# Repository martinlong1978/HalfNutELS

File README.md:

# HalfNutELS — Electronic Leadscrew

An open-source **Electronic Leadscrew (ELS)** controller for a metalworking lathe, running on an
**ESP32-WROOM-32E**, with a 320×240 LVGL TFT interface, a 3×3 keypad and a rotary encoder.

An electronic leadscrew replaces a lathe's mechanical change gears / gearbox. Instead of a train of
gears mechanically coupling the spindle to the leadscrew, an **encoder** on the spindle is read by
the microcontroller, which drives a **stepper motor** on the leadscrew in software-defined ratio to
the spindle. This lets you select any thread pitch or feed rate electronically — for single-point
threading and powered feeding — without swapping gears.

> **Note on the name:** *half-nuts* are the split nut a lathe operator clamps onto the leadscrew to
> engage a threading pass — and the part an electronic leadscrew makes redundant, since the pitch is
> now held in software rather than caught on a thread-dial line. The project was called *TeensyELS*
> until August 2026, after the Teensy it began on; Teensy support was removed well before the rename,
> and naming firmware after its microcontroller was a poor idea in the first place. The upstream
> project it derives from is still called TeensyELS — see [Attribution](#attribution). The KiCad
> projects and the board silkscreen also still carry the old name.

> **Note on the hardware:** the current design is the **LVGL board** in
> [`kicad/LVGL/`](kicad/LVGL/) (silkscreened `TeensyELS v0.6`, pre-rename) — an ESP32-WROOM-32E
> soldered directly to the board, driving a 320×240 SPI TFT through LVGL. It is the only board design
> in the repository — the earlier revisions have been removed.

---

## Contents
- [Features](#features)
- [Hardware / Components](#hardware--components)
- [Enclosure & keycaps](#enclosure--keycaps)
- [Getting boards made (PCB)](#getting-boards-made-pcb)
- [Building & flashing the firmware](#building--flashing-the-firmware)
- [Connecting & configuring](#connecting--configuring)
- [Operating the ELS — controls & display](#operating-the-els--controls--display)
- [Cutting a thread](#cutting-a-thread)
- [Firmware updates](#firmware-updates)
- [Settings reference](#settings-reference)
- [Diagnostics](#diagnostics)
- [Testing / development](#testing--development)
- [License](#license)
- [Attribution](#attribution)
- [Safety disclaimer](#safety-disclaimer)

---

## Features

- **Threading** — synchronise the leadscrew to the spindle at a selectable thread pitch for
  single-point threading. Metric (mm/rev) and imperial (TPI) thread pitch tables are built in.
- **Reverse threading** — a thread mode that runs the carriage in the opposite direction (from the
  left stop toward the right) for left-hand threads or threading away from a shoulder.
- **Feeding** — powered feed at a selectable feed rate (mm/rev metric, or thou/rev imperial).
- **Feed / thread mode switching** from the panel; **metric / imperial** from the menu.
- **Jog** — move the carriage left/right under power. Supports both an interactive "hold to jog"
  mode and a "jog to stop" mode.
- **End stops / stop positions** — set left and right stop positions so the carriage automatically
  decelerates and stops at a repeatable point (useful for threading up to a shoulder).
- **Thread sync** — the leadscrew tracks the spindle's angular position so a partially cut thread can
  be picked up again on the next pass.
- **Motion lockout** — while the carriage is under power the panel answers only **HALT** and
  **ENABLE**. There is no lock key to remember: the machine locks itself exactly when it matters.
  (This replaced an explicit button lock, which had to be unlocked at every power-on.)
- **DRO** — carriage position referenced to an endstop, with a travel bar that doubles as a readout.
- **Dark and light themes**, selectable on the device.
- **Web-based configuration** — all lathe parameters (encoder PPR, stepper PPR, gearbox ratio,
  leadscrew pitch, speeds, acceleration) plus WiFi credentials are configured over a built-in web
  page; settings are stored in the ESP32's non-volatile flash.
- **Over-the-air (OTA) firmware update** — pulls the latest [GitHub release](https://github.com/martinlong1978/HalfNutELS/releases)
  from a stable permalink and skips the download if the device is already on that version.
- **Motion-trace capture** — records ~25 s of following error, loop timing and spindle deltas and
  uploads it as CSV for offline analysis. Built to diagnose a threading glitch; kept because it is
  the fastest way to answer "is the fault in the maths or in the timing?".
- **On-device display** — a 240×320 ST7789 SPI TFT, driven in landscape (**320×240**) via **LVGL**,
  shows current mode, pitch, spindle RPM and status.
- **Rotary encoder** — turns to adjust whatever the panel currently has focused; its
  built-in LED shows the run state at a glance (the firmware drives the red and green channels,
  alternating them to flash a two-colour status).

---

## Hardware / Components

The controller is built around a custom PCB. KiCad design files, gerbers and fabrication outputs are
in the [`kicad/`](kicad/) directory.

**The current design is [`kicad/LVGL/`](kicad/LVGL/)** — silkscreened *TeensyELS v0.6*, a **4-layer**
board of roughly **113 × 109 mm**. It does not socket a dev-board module: the **ESP32-WROOM-32E is
soldered directly to the PCB**, the display is a separate SPI TFT module on a 14-pin socket, and the
board is designed to be **SMT-assembled** (JLCPCB) with only the connectors and the rotary encoder
hand-soldered.

### Bill of materials

**SMT parts** — taken from the JLCPCB production BOM
([`kicad/LVGL/jlcpcb/production_files/BOM-TeensyELS.csv`](kicad/LVGL/jlcpcb/production_files/BOM-TeensyELS.csv)),
cross-checked against the schematic:

| Designator(s) | Qty | Part / Value | Footprint | LCSC |
|---|---|---|---|---|
| U2 | 1 | **ESP32-WROOM-32E** — main controller (Wi-Fi module, 4 MB flash) | ESP32-WROOM-32D | C701342 |
| U1 | 1 | AMS1117-3.3 — 5 V → 3.3 V regulator | SOT-223-3 | C6186 |
| Q2–Q7, Q9 | 7 | BSS138 N-channel MOSFET (3.3 V ↔ 5 V level shifting, LED drive) | SOT-23 | C7420339 |
| C1 | 1 | 10 µF capacitor | 0805 | C15850 |
| C2 | 1 | 22 µF capacitor | 0805 | C45783 |
| C3, C4 | 2 | 0.1 µF capacitor | 0805 | C49678 |
| R1–R8, R11, R12, R17, R18, R20, R21 | 14 | 10 kΩ resistor (pull-ups) | 0805 | C17414 |
| R9, R10, R19 | 3 | 330 Ω resistor (encoder LED series) | 0805 | C17630 |
| R13, R14 | 2 | 0 Ω link (encoder direct-connect option) | 0805 | C17477 |
| SW1–SW10 | 10 | Omron B3FS-101xP **SMD** tactile switch (SW2–SW10 = the 3×3 keypad; SW1 = stepper-enable override) | SW_SPST_Omron_B3FS-101xP | C231324 |
| J5 | 1 | 2×3 1.27 mm header — UART programming header | PinHeader 2x03 1.27 mm SMD | C42372553 |

**Not fitted (DNP)** — an alternative encoder input path, see the note below:

| Designator(s) | Qty | Part / Value |
|---|---|---|
| Q1, Q8 | 2 | BSS138 (encoder level-shift MOSFETs) |
| R15, R16 | 2 | 1 kΩ (gate resistors for Q1/Q8) |

**Through-hole / hand-soldered parts** — these are *not* in the assembly BOM and must be fitted
yourself:

| Designator | Qty | Part | Purpose |
|---|---|---|---|
| J1 | 1 | Shielded RJ45 jack (RCH RC01937) | **Stepper driver** — step / dir / enable / alarm, at 5 V |
| J2 | 1 | JST-XH 4-pin vertical header (B4B-XH-A) | **Spindle encoder** — 5 V, GND, A, B |
| J3 | 1 | 1×14 2.54 mm socket | **Display module** (see below) |
| J4 | 1 | 2-pin 5.08 mm screw terminal (CUI TB007-508-02) | **5 V power input** |
| E1 | 1 | Illuminated (RGB) rotary encoder, SparkFun footprint | Pitch / jog-rate selection + status LED |

Not on the board at all, but **required to build a working ELS**:

- A **240×320 SPI TFT module** with the common **14-pin 2.54 mm header** (9 display pins + 5 touch
  pins). The firmware drives it as an **ST7789** and uses it in landscape, 320×240. Only the display
  pins are wired — the 5 touch pins are unconnected, and the backlight pin is tied to +3.3 V, so the
  backlight is permanently on and is *not* under software control.
- A **spindle encoder** — a quadrature encoder on the lathe spindle, wired to **J2** (not J1). The
  default configuration assumes **1200 PPR** (see [Settings reference](#settings-reference)).
- A **stepper motor + driver** for the leadscrew, wired to the RJ45 jack **J1**. The board provides
  step, dir and enable as 5 V open-drain outputs (10 kΩ pull-ups to +5 V) and accepts the driver's
  alarm output. The default configuration assumes a **400 step/rev** stepper.
- A **5 V supply** into J4 (which also feeds the encoder and the 3.3 V regulator), plus a suitable
  **power supply for the stepper driver** itself.
- A **USB-to-serial adapter** for flashing — the board has no USB connector, see
  [Building & flashing](#building--flashing-the-firmware).

> **Encoder input — 3.3 V vs 5 V.** J2's A/B pins can reach the ESP32 two ways: directly through the
> 0 Ω links **R13/R14**, or level-shifted through **Q1/Q8 + R15/R16**. The assembly BOM fits the 0 Ω
> links and leaves the MOSFET path off, i.e. it expects an encoder whose outputs are safe to feed
> straight into a 3.3 V GPIO. If your encoder swings to 5 V, fit Q1/Q8 and R15/R16 and leave R13/R14
> off. **Please verify against the schematic** ([`kicad/LVGL/TeensyELS.kicad_sch`](kicad/LVGL/TeensyELS.kicad_sch))
> before ordering.

### Connectors

| Ref | Type | Pinout |
|---|---|---|
| **J4** | 2-pin screw terminal | 1 = GND, 2 = **+5 V in** |
| **J2** | JST-XH 4-pin | 1 = +5 V, 2 = GND, 3 = encoder B, 4 = encoder A |
| **J1** | RJ45 (shielded) | 1 = ALARM (in), 3 = ENABLE, 5 = DIR, 7 = STEP; 2/4/6/8 = GND; shield = GND. All 5 V. |
| **J3** | 1×14 socket (display) | 14 = VCC, 13 = GND, 12 = CS, 11 = RESET, 10 = DC, 9 = MOSI, 8 = SCK, 7 = LED (tied to +3.3 V), 6 = MISO (not connected to the ESP32); 5–1 = touch pins, unconnected |
| **J5** | 2×3 1.27 mm | 1 = EN, 2 = +3.3 V, 3 = TXD, 4 = GND, 5 = RXD, 6 = BOOT (GPIO0) |
| **SW1** | on-board push button | Pulls the stepper **ENABLE** line to +5 V — a manual override, independent of the firmware |

### Pin assignments (ESP32)

Defined in [`lib/config/board.h`](lib/config/board.h) and matching the LVGL schematic:

| Function | GPIO |
|---|---|
| Spindle encoder A / B (J2) | 35 / 34 |
| UI rotary encoder A / B (E1) | 39 / 36 |
| Encoder status LED — red / green / blue (E1) | 22 / 21 / 12 |
| Leadscrew step | 25 |
| Leadscrew direction | 26 |
| Stepper enable | 17 |
| Stepper driver alarm input | 27 *(wired on the board; not read by the current firmware)* |
| Keypad matrix rows (H1/H2/H3) | 32 / 33 / 2 |
| Keypad matrix columns (V1/V2/V3) | 13 / 14 / 15 |
| TFT display (MOSI/SCLK/CS/DC/RST) | 19 / 18 / 5 / 16 / 23 |
| TFT backlight (`TFT_BL`) | 4 *(defined in the build flags but **not connected** on this board)* |
| Programming UART TXD / RXD (J5) | 1 / 3 |

> The A/B pins of both encoders are swapped in `board.h` relative to the schematic net names — that
> only sets which way round the counting goes, and is deliberate.

> **The keypad matrix is polled, not interrupt-driven.** A 2 ms task scans it and a host-tested
> debounce ([`lib/keyscan/`](lib/keyscan/)) turns the readings into press / click / hold / release
> events. Edge interrupts were tried and removed — see [`docs/keypad-audit.md`](docs/keypad-audit.md)
> for why they cannot be made reliable here.

---

## Enclosure & keycaps

Two 3D models are provided in [`cad/`](cad/), both as **STEP** files:

| File | What it is |
|---|---|
| [`cad/Keycaps.step`](cad/Keycaps.step) | Keycaps for the 3×3 keypad |
| [`cad/Enclosure.step`](cad/Enclosure.step) | A full enclosure for the controller |

STEP is a neutral CAD interchange format — it imports into FreeCAD, Fusion and SolidWorks, so the
models can be measured and edited before you make anything from them. To 3D-print a part, convert it
to **STL** or **3MF** in your CAD tool and slice that; the same STEP file can go to a machine shop if
you would rather have the enclosure cut than printed.

The keycaps cover the nine keys of the panel keypad — which legend belongs on which cap is set out in
[Keypad layout](#keypad-layout), along with the warning to re-confirm the scan codes before making
caps if you have rewired the loom. For reference when checking fit, the board itself is roughly
**113 × 109 mm**.

> No print settings, material or fastener sizes are specified with these models. Check them against
> your own printer and hardware before committing to a run.

---

## Getting boards made (PCB)

Fabrication outputs for the LVGL board are pre-generated under [`kicad/LVGL/`](kicad/LVGL/). The
JLCPCB set in [`kicad/LVGL/jlcpcb/production_files/`](kicad/LVGL/jlcpcb/production_files/) is the one
to use — it is the only output that carries **LCSC part numbers**, and its BOM matches the assembly
intent (SMT parts only, encoder level-shift path left off).

> ⚠️ **Do not use `kicad/LVGL/production/bom.csv` or `positions.csv`.** Those files are stale
> carry-overs from an earlier board revision — they still list a socketed display module and a Teensy
> footprint, neither of which exists on this board. Regenerate them from KiCad if you need them.

### Option A — JLCPCB (bare board, or with assembly)

1. Go to [jlcpcb.com](https://jlcpcb.com) and click **Add gerber file**.
2. Upload [`kicad/LVGL/jlcpcb/production_files/GERBER-TeensyELS.zip`](kicad/LVGL/jlcpcb/production_files/GERBER-TeensyELS.zip)
   (do **not** unzip it — upload the zip directly). The KiCad-native export
   [`kicad/LVGL/gerbers.zip`](kicad/LVGL/gerbers.zip) is equivalent if you prefer it.
3. Confirm the auto-detected settings: **Layers = 4**, and the board dimensions shown in the preview
   (≈113 × 109 mm). Choose thickness, colour, surface finish, etc. as desired.
4. *(Optional — assembly / PCBA)* Enable **PCB Assembly** (top side only), then upload:
   - **BOM:** [`kicad/LVGL/jlcpcb/production_files/BOM-TeensyELS.csv`](kicad/LVGL/jlcpcb/production_files/BOM-TeensyELS.csv)
   - **Pick-and-place / CPL:** [`kicad/LVGL/jlcpcb/production_files/CPL-TeensyELS.csv`](kicad/LVGL/jlcpcb/production_files/CPL-TeensyELS.csv)
5. Review the placement in JLCPCB's assembly preview — pay particular attention to the orientation of
   U1, U2 and the MOSFETs — resolve any part substitutions, and place the order.
6. Hand-solder the through-hole parts afterwards: **J1, J2, J3, J4 and the rotary encoder E1**.

### Option B — PCBWay

1. Go to [pcbway.com](https://www.pcbway.com) and choose **Quick-order PCB → Add Gerber File**.
2. Upload [`kicad/LVGL/gerbers.zip`](kicad/LVGL/gerbers.zip).
3. Confirm layer count (**4**) and dimensions, pick your board options, and add to cart.
4. *(Optional — assembly)* Choose **Turnkey Assembly** and provide the BOM and pick-and-place files
   above. PCBWay does not use LCSC numbers directly, so expect to confirm equivalents for each line.

---

## Building & flashing the firmware

The firmware is a [PlatformIO](https://platformio.org/) project (see
[`platformio.ini`](platformio.ini)).

### 1. Install PlatformIO

Install the [PlatformIO IDE extension for VS Code](https://platformio.org/install/ide?install=vscode),
or the [PlatformIO Core CLI](https://docs.platformio.org/en/latest/core/installation/index.html).
PlatformIO will automatically download the ESP32 toolchain and the libraries listed in
`platformio.ini` on first build.

### 2. Connect a USB-to-serial adapter

The LVGL board has **no USB connector** — the ESP32-WROOM-32E is programmed through the 2×3 1.27 mm
header **J5**:

| J5 pin | Signal | Adapter |
|---|---|---|
| 1 | EN (reset) | RTS *(optional — for auto-reset)* |
| 2 | +3.3 V | — *(do not back-feed if the board is powered from J4)* |
| 3 | TXD (ESP32 → adapter) | RX |
| 4 | GND | GND |
| 5 | RXD (adapter → ESP32) | TX |
| 6 | BOOT (GPIO0) | DTR *(optional — for auto-bootloader)* |

Use a **3.3 V** adapter. If you only wire TX/RX/GND, you must put the module into the bootloader by
hand — hold GPIO0 low, pulse EN low and release it, then start the upload.

### 3. Build & upload

There are two ESP32 build environments:

- **`esp32dev_usb`** — build and flash over the serial adapter. This is the environment to use for
  normal development. Edit the `upload_port` in `platformio.ini` (default `COM14`) to match the port
  your adapter enumerates as.

  ```sh
  pio run -e esp32dev_usb -t upload
  ```

- **`esp32dev_publish`** — a release build that uses a custom upload command (`publish.cmd`) for
  producing/publishing an OTA image rather than a direct flash.

  ```sh
  pio run -e esp32dev_publish
  ```

Both ESP32 environments still declare `board = lilygo-t-display`. That is just a convenient 4 MB
ESP32-D0WD profile and is compatible with the WROOM-32E module — the display geometry that matters is
set explicitly in the build flags (`TFT_WIDTH=240`, `TFT_HEIGHT=320`, ST7789 driver, SPI pins), and a
custom 4 MB partition table (`my_4MB.csv`) is used.

---

## Connecting & configuring

Configuration is done over WiFi through a built-in web page — there is no need to recompile to
retune the firmware for your lathe.

1. **Enter configuration mode.** The device starts a WiFi **Access Point** on first boot (when no
   valid settings are stored yet), whenever you **hold `OK` — the centre key — while powering on**,
   or from the **Wi-Fi setup** menu tile. See [`src/main.cpp`](src/main.cpp).
   - AP SSID: **`ELS_Wifi`**
   - AP password: **`123456789`**
2. **Connect** your phone or laptop to that access point. The SSID, password and IP address are shown
   on the device's display, along with a QR code for the WiFi credentials.
3. **Open the device in a browser.** The firmware runs a **captive portal** — a catch-all DNS server
   plus the usual Android/Apple/Windows detection URLs — so most phones will pop the configuration
   page up automatically on connecting. If yours doesn't, browse to the IP shown on the display
   (typically `192.168.4.1`) to reach the *ELS Setup* page.

| First-run setup screen | Connected |
|---|---|
|  |  |

4. **Fill in the settings** (see [Settings reference](#settings-reference)) and press **Submit**.
   Settings are written to the ESP32's flash. Press **Reset** on the page (or power-cycle) to reboot
   into normal operation with the new settings.

---

## Operating the ELS — controls & display

The panel is nine keys and a rotary encoder. Everything below is driven from those.

> Every screenshot in this README is rendered from the **real display code** on a host machine
> (`bash tools/screenshot/render.sh`), so what you see here is what the panel draws.

### Power-on

The splash holds for **two seconds** on every normal boot, then the rest screen replaces it. It
carries the running **firmware version**, which is the quickest way to check what a machine is on
without opening the menu — worth a glance after an over-the-air update. It is drawn on whichever
theme is stored, and it is skipped entirely on the first-run setup path, where the Wi-Fi credentials
matter more than the branding.

### The rest screen

Top row: **mode**, **units**, **sync state**, **spindle RPM**. The large figure is the current pitch
or feed rate. Below it the **travel bar** shows the carriage between the endstops — it doubles as a
DRO readout. The chip at the bottom left is the **machine state** (`IDLE`, `FEED`, `THREAD`, `JOG`).

| Metric thread | Imperial feed | Spindle running backwards |
|---|---|---|
|  |  |  |

### Keypad layout

Selectors along the top, the two actuators plus `OK` in the middle where your thumbs sit, and
machine state along the bottom:

| | Left | Centre | Right |
|---|---|---|---|
| **Top row** | `MODE` | `RATE` | `STOPS` |
| **Middle row** | `◀` | `OK` | `▶` |
| **Bottom row** | `HALT` | `MENU` | `ENABLE` |

The small numbers on the diagram are the **matrix scan codes** — useful when wiring a panel or
reading a debug trace. They are `code = H | V << 3`, with the H rows on GPIO 32 / 33 / 2 and the V
columns on GPIO 13 / 14 / 15; the mapping is defined in [`lib/config/board.h`](lib/config/board.h).
If you rewire the loom the nine codes stay distinct but the assignment transposes, so re-confirm by
pressing each key and reading its code before making new caps.

The three top keys choose **what the arrows drive**; the arrows are the only actuators. That is the
*focus model*: press a selector, a panel opens, the arrows adjust it, `OK` commits. Focus returns to
jog on its own after 4 seconds.

*(Holding `OK` during power-on boots into Wi-Fi configuration mode.)*

### Arrows at rest — jog

With nothing else focused the arrows move the carriage, and what they do depends on whether that
side has a stop set — the machine already knows which behaviour you mean:

| | Stop **set** on that side | Stop **unset** |
|---|---|---|
| **Click** | Run under power to the stop, then hold | — |
| **Hold** | (same as click) | Jog continuously while held; decelerate on release |

A second press of the same arrow during a powered run **cancels** it.

### Key reference

| Control | Click | Hold |
|---|---|---|
| `MODE` | Open the mode picker — Feed / Thread R / Thread L | — |
| `RATE` | Open the pitch picker | — |
| `STOPS` | Open the stops panel | Clear **both** stops, after a 1 s confirm |
| `◀` / `▶` | Jog, or run to the stop (see above) | Continuous jog when no stop is set |
| `OK` | Jog-speed picker (at rest); commit and close (in a picker) | **Zero the DRO** here |
| `MENU` | Open the menu carousel; press again to close | — |
| `HALT` | Decelerate to a stop. **Always live**, from any screen | — |
| `ENABLE` | Engage / disengage the leadscrew | — |
| Encoder | Adjust whatever is focused (pitch at rest) | — |

Pressing the **same selector twice** closes its panel again — `MODE`, `RATE`, `STOPS` and `MENU` all
toggle.

**`ENABLE` takes two presses when a panel is open**: the first dismisses the panel, the second
engages. Engaging is a commitment to cut, and it should not happen while a picker is covering the
state chip.

### The selector panels

| `MODE` | `RATE` | `OK` — jog speed |
|---|---|---|
|  |  |  |

**Stops.** The panel shows the travel bar full width with both markers and the live position.
Setting a stop is cheap to undo; clearing one loses a position you may have spent time finding, so
the two gestures are deliberately asymmetric:

| Gesture | Effect |
|---|---|
| `◀` click, left stop unset | Set the left stop **here** |
| `◀` click, left stop set | Prompts "hold to clear" — no action |
| `◀` hold, left stop set | Clear the left stop |
| `STOPS` hold | Clear **both**, after a 1 s confirm bar |

`▶` is the mirror.

| Stops panel | Clearing both — confirm bar filling |
|---|---|
|  |  |

### The menu

`MENU` opens a horizontal carousel; the arrows move between tiles and `OK` activates. The carousel
**wraps**, so the far end is one press away in the other direction. Tiles never edit in place — `OK`
either performs a one-shot action or opens the matching panel.

| Tile | `OK` does |
|---|---|
| **Units** | Toggle mm / inch |
| **Theme** | Toggle dark / light (persisted) |
| **DRO datum** | Choose which endstop is zero (persisted) |
| **Jog speed** | Open the jog-speed picker |
| **Sync** | Set a thread sync point at the current spindle angle and carriage position |
| **Software update** | Check for and install a new firmware release |
| **Wi-Fi setup** | Reboot into the configuration access point |
| **Diagnostics** | Live following error, spindle vs leadscrew rates, sync anchor |
| **About** | Firmware version, IP address, uptime |
| **Debug capture** | Arm a motion-trace capture |

A tile that cannot act right now renders as **UNAVAILABLE** with the reason on the hint row, rather
than vanishing — so the tile numbering never shifts under you:

| Sync, outside a thread mode | Update, while the carriage is moving |
|---|---|
|  |  |

### The DRO

A position is meaningless without a zero, and "wherever the machine happened to boot" is the worst
available choice — so **zero is referenced to an endstop**. First match wins:

| # | Condition | Datum |
|---|---|---|
| 1 | Manual zero set (`OK` held) | That position, tagged `MAN` |
| 2 | Both stops set | The one chosen on the **DRO datum** tile |
| 3 | Exactly one stop set | That one — the preference cannot be honoured |
| 4 | Neither stop set | Power-on origin, flagged `REL` |

Position increases to the **right**, so a right-hand datum counts negative leftward — ordinary DRO
behaviour. The readout flashes for about a second whenever the datum moves, because setting a second
stop can hand zero to the other end and the numbers will jump.

| DRO datum picker | Refused while under power |
|---|---|
|  |  |

### While the carriage is moving

The panel answers **only `HALT` and `ENABLE`**. No menus, no pickers, no settings — and any open
panel closes itself when motion starts. Your attention belongs on the tool and the work, not the
screen. `HALT` is the reflex; `ENABLE` is the deliberate one.

The one exception is **Diagnostics**, which stays up through jogging and cutting because watching it
while the machine runs is the entire point. `OK` clears it.

| Jogging | Cutting | Decelerating |
|---|---|---|
|  |  |  |

---

## Cutting a thread

1. **Set the mode.** `MODE`, arrows to **Thread R** (or **Thread L** for a left-hand thread), `OK`.
2. **Set the pitch.** `RATE`, arrows to your pitch, `OK`. The **Units** tile switches between metric
   and TPI; the controller remembers a pitch per mode-and-unit pair, so switching back and forth
   does not lose your place.
3. **Set the stops.** Jog to where the thread should end — usually just short of the shoulder — press
   `STOPS`, then `◀` or `▶` to set that stop. Do the same at the starting end. The carriage now
   decelerates and stops there on every pass, which is what makes threading to a shoulder
   repeatable.
4. **Return to the start** and take your first depth of cut on the cross-slide.
5. **Press `ENABLE`.** The leadscrew waits for the spindle to come round to the sync point, then
   tracks the thread to the far stop and stops.
6. **Retract, return the carriage, advance the depth, `ENABLE` again.** The sync point is preserved,
   so every pass follows the same helix.

**Picking up an existing thread.** Stop the spindle, hand-position the tool so it sits in an existing
groove, then use the **Sync** menu tile. That declares "this spindle angle and this carriage position
are in sync", and every later engagement re-enters that same helix instead of ploughing a new groove
across it. The **Diagnostics** screen shows which anchor is currently in use.

### Feeding

Same flow, simpler: `MODE` → **Feed**, `RATE` → your feed rate (mm/rev, or thou/rev in imperial), set
a stop if you want the cut to end somewhere repeatable, then `ENABLE`.

---

## Firmware updates

**From the device.** `MENU` → **Software update** → `OK`. The controller checks the latest
[GitHub release](https://github.com/martinlong1978/HalfNutELS/releases), tells you if you are already
on it, and otherwise downloads and flashes, showing progress on screen. It uses the Wi-Fi credentials
from the setup page.

| Checking | Already current | Downloading |
|---|---|---|
|  |  |  |

**Over USB.** `pio run -e esp32dev_usb -t upload`, via the J5 serial header.

**Publishing your own.** Bump `FIRMWARE_VERSION` in [`include/version.h`](include/version.h), then
`pio run -e esp32dev_publish` and `bash scripts/release.sh` (needs the `gh` CLI). The OTA permalink
resolves to whatever is marked *latest*, so publish full releases rather than drafts.

---

## Settings reference

Settings come in two kinds, and the split is deliberate.

**Lathe geometry is web-only.** Encoder PPR, stepper PPR, direction, gearbox ratio, leadscrew pitch,
jog speed, acceleration and max speed are *commissioning* values: set once over Wi-Fi with the lathe
offline, and changed only there. The device never writes them. Getting one wrong turns every
subsequent cut into scrap, so they are deliberately not reachable from a panel you might brush past
mid-job.

**Preferences are on-device.** Theme and DRO datum are the things worth changing mid-session, and
they live on the menu. Saving them is refused while the carriage is under power.

### Wi-Fi / update settings

| Web label | Field | Meaning |
|---|---|---|
| **Wi-Fi network** | `ssid` | Network the device joins for OTA updates and trace uploads. Up to 31 chars. |
| **Wi-Fi password** | `password` | Up to 62 chars. Leave blank for an open network. |
| **Firmware update URL** | `url` | Where **Software update** pulls from. Defaults to this repo's `latest` release permalink. |
| **Debug capture URL** | `debugUrl` | Where the **Debug capture** tile POSTs its motion trace. Blank disables sending. See [`tools/debugsink/`](tools/debugsink/). |

### Lathe geometry

Defaults are in [`lib/config/latheconfig.h`](lib/config/latheconfig.h).

| Web label | Field | Default | Units | Meaning |
|---|---|---|---|---|
| **Spindle encoder** | `spindleEncoderPpr` | `1200` | pulses/rev | Pulses per spindle revolution. Must match your encoder or every pitch is wrong. |
| **Stepper** | `stepperPpr` | `400` | steps/rev | Steps per stepper revolution — full steps × the microstepping set on the driver. |
| **Invert motor direction** | `invertDirection` | `true` | boolean | Flips the direction sense so left and right match your lathe. |
| **Gearbox ratio** | `gearboxRatioNumerator` / `gearboxRatioDenominator` | `2` / `1` | ratio | Any mechanical reduction between stepper and leadscrew. Effective ratio = numerator ÷ denominator. |
| **Leadscrew pitch** | `leadscrewPitchMm` | `2.54` | mm/rev | Carriage travel per leadscrew revolution. |
| **Jog speed** | `jogSpeed` | `40` | mm/s | Full-speed jog. The on-device jog-speed picker selects a percentage of this. |
| **Acceleration** | `leadscrewAcceleration` | `150` | mm/s² | Ramp used for all leadscrew motion. |
| **Max speed** | `leadscrewMaxSpeed` | `40` | mm/s | Upper limit for leadscrew motion. |

Steps/mm, pulses/sec and the pulse timings are derived from these once at startup
([`lib/config/latheconfig.cpp`](lib/config/latheconfig.cpp)); the metric and imperial pitch tables
are in [`lib/config/config.h`](lib/config/config.h).

### On-device preferences

| Setting | Where | Options |
|---|---|---|
| **Units** | `MENU` → Units | mm / inch |
| **Theme** | `MENU` → Theme | Dark / light — persisted |
| **DRO datum** | `MENU` → DRO datum | Which endstop is zero when both are set — persisted |
| **Jog speed** | `OK` at rest, or `MENU` → Jog speed | 1 %, 5 %, 10 %, 25 %, 50 %, 100 % of the configured jog speed |

*The light theme. Both are designed for the panel rather than inverted from each other.*

### Where settings live, and how to wipe them

Settings are stored as a raw struct in flash, guarded by a validity sentinel (`CHECKVALUE` in
[`lib/config/latheconfig.h`](lib/config/latheconfig.h)). If the stored value does not match the
firmware's, the whole blob is discarded and the device boots into first-run AP setup — which is how
a firmware change that moves the layout avoids reading someone else's bytes as your geometry.

To clear everything deliberately — including Wi-Fi credentials — use **Factory reset** at the bottom
of the web setup page. It asks for confirmation, then reboots into first-run setup.

---

## Diagnostics

`MENU` → **Diagnostics** shows live following error, spindle and leadscrew rates, and which sync
anchor the helix is currently pinned to. Unlike every other screen it **stays up while the machine
runs**, because that is when its numbers mean anything — at rest they are all zero. `OK` clears it.

| Diagnostics | Following error | Manual sync anchor |
|---|---|---|
|  |  |  |

**Motion-trace capture.** `MENU` → **Debug capture** arms a recorder that samples following error,
loop timing and spindle deltas at 40 Hz for about 25 seconds, then uploads it as CSV to the
**Debug capture URL** once the carriage is at rest. [`tools/debugsink/`](tools/debugsink/) has a
stdlib-only Python receiver, a PHP drop-in and an analysis script that flags direction reversals and
correlates error spikes against loop stalls — which is what distinguishes "the maths is wrong" from
"the loop is being starved".

---

## Testing / development

The motion/business logic is designed to be unit-testable on your host machine without any hardware,
using the **`native`** PlatformIO environment (the project's default env), which builds against
GoogleTest/GMock:

```sh
pio test -e native
```

The suite is 455 cases and covers the parts where a mistake is expensive: the UI focus state machine,
the keypad debounce and gesture recognition, DRO datum resolution, thread-sync anchoring, stop
handling, the config layout in flash, and the trace capture. Motion tests drive a virtual clock so a
spindle can be turned at a chosen rate without hardware.

### Seeing the screens without a lathe

```sh
bash tools/screenshot/render.sh
```

Renders the **real** `Display` class on the host and writes one 320×240 PNG per scenario to
`tools/screenshot/out/` — every screenshot in this README came from it. Only `Arduino.h`, `SPI.h` and
`TFT_eSPI.h` are shimmed; the display, DRO, UI state and LVGL build are the production code, against
the project's own `lv_conf.h`. Scenes drive it through the same public inputs the firmware does, so a
screen the keypad cannot reach cannot be screenshotted either.

`native` is built with `-D PIO_UNIT_TESTING=1`, which selects host test doubles in place of the
ESP32 hardware classes. See the [`test/`](test/) directory for the test suites.

---

## License

This project is licensed under the **GNU General Public License v3.0**. See the [`LICENSE`](LICENSE)
file for the full text.

You are free to use, study, share and modify this software under the terms of the GPLv3. Derivative
works and distributed modified versions must also be made available under the GPLv3.

---

## Attribution

This firmware is **derived from the "TeensyELS" project by NoEngineerHere** (associated with the
*Not an Engineer* YouTube channel), with thanks to the upstream author for the original work this
builds on:

- **Upstream repository:** https://github.com/NoEngineerHere/TeensyELS

The derivation is evidenced by this repository's original name (*TeensyELS*, matching upstream, until
the August 2026 rename to *HalfNutELS*), the near-verbatim original `README.md` stub, a shared project
structure (PlatformIO project, `native` GoogleTest environment, `kicad/` hardware directory), and this
repo's history migrating from Teensy to ESP32 (Teensy support removed in commit `cbd1b22`).

**Licensing:** the project owner has confirmed that release under the GPLv3 is cleared.

> A separate, well-known project — **Clough42 "electronic-leadscrew"** by James Clough
> (https://github.com/clough42/electronic-leadscrew) — is a *different* ELS design (TI F280049C
> microcontroller, MIT-licensed) and is **not** the upstream of this code; it is noted only to avoid
> confusion with the best-known open ELS project.

---

## Safety disclaimer

**This project controls moving machinery and is provided with no warranty of any kind.**

A lathe with a powered leadscrew can cause **serious injury or death** and can destroy tooling and
workpieces. An electronic leadscrew removes the mechanical safeguards of change gears — a software
bug, miswired encoder, wrong setting, or loss of spindle sync can drive the carriage unexpectedly,
including into the chuck.

- Use at your **own risk**. You are responsible for the safe design, wiring, configuration and
  operation of your machine.
- **Test thoroughly with the spindle stopped and, where possible, the leadscrew disconnected** before
  cutting.
- Always know where your **stop positions** and emergency stop are before engaging.
- This firmware is **experimental** and, as noted above, may contain bugs affecting speed and
  acceleration limits.

As stated in the GPLv3, this software is distributed in the hope that it will be useful, but
**WITHOUT ANY WARRANTY**; without even the implied warranty of MERCHANTABILITY or FITNESS FOR A
PARTICULAR PURPOSE.

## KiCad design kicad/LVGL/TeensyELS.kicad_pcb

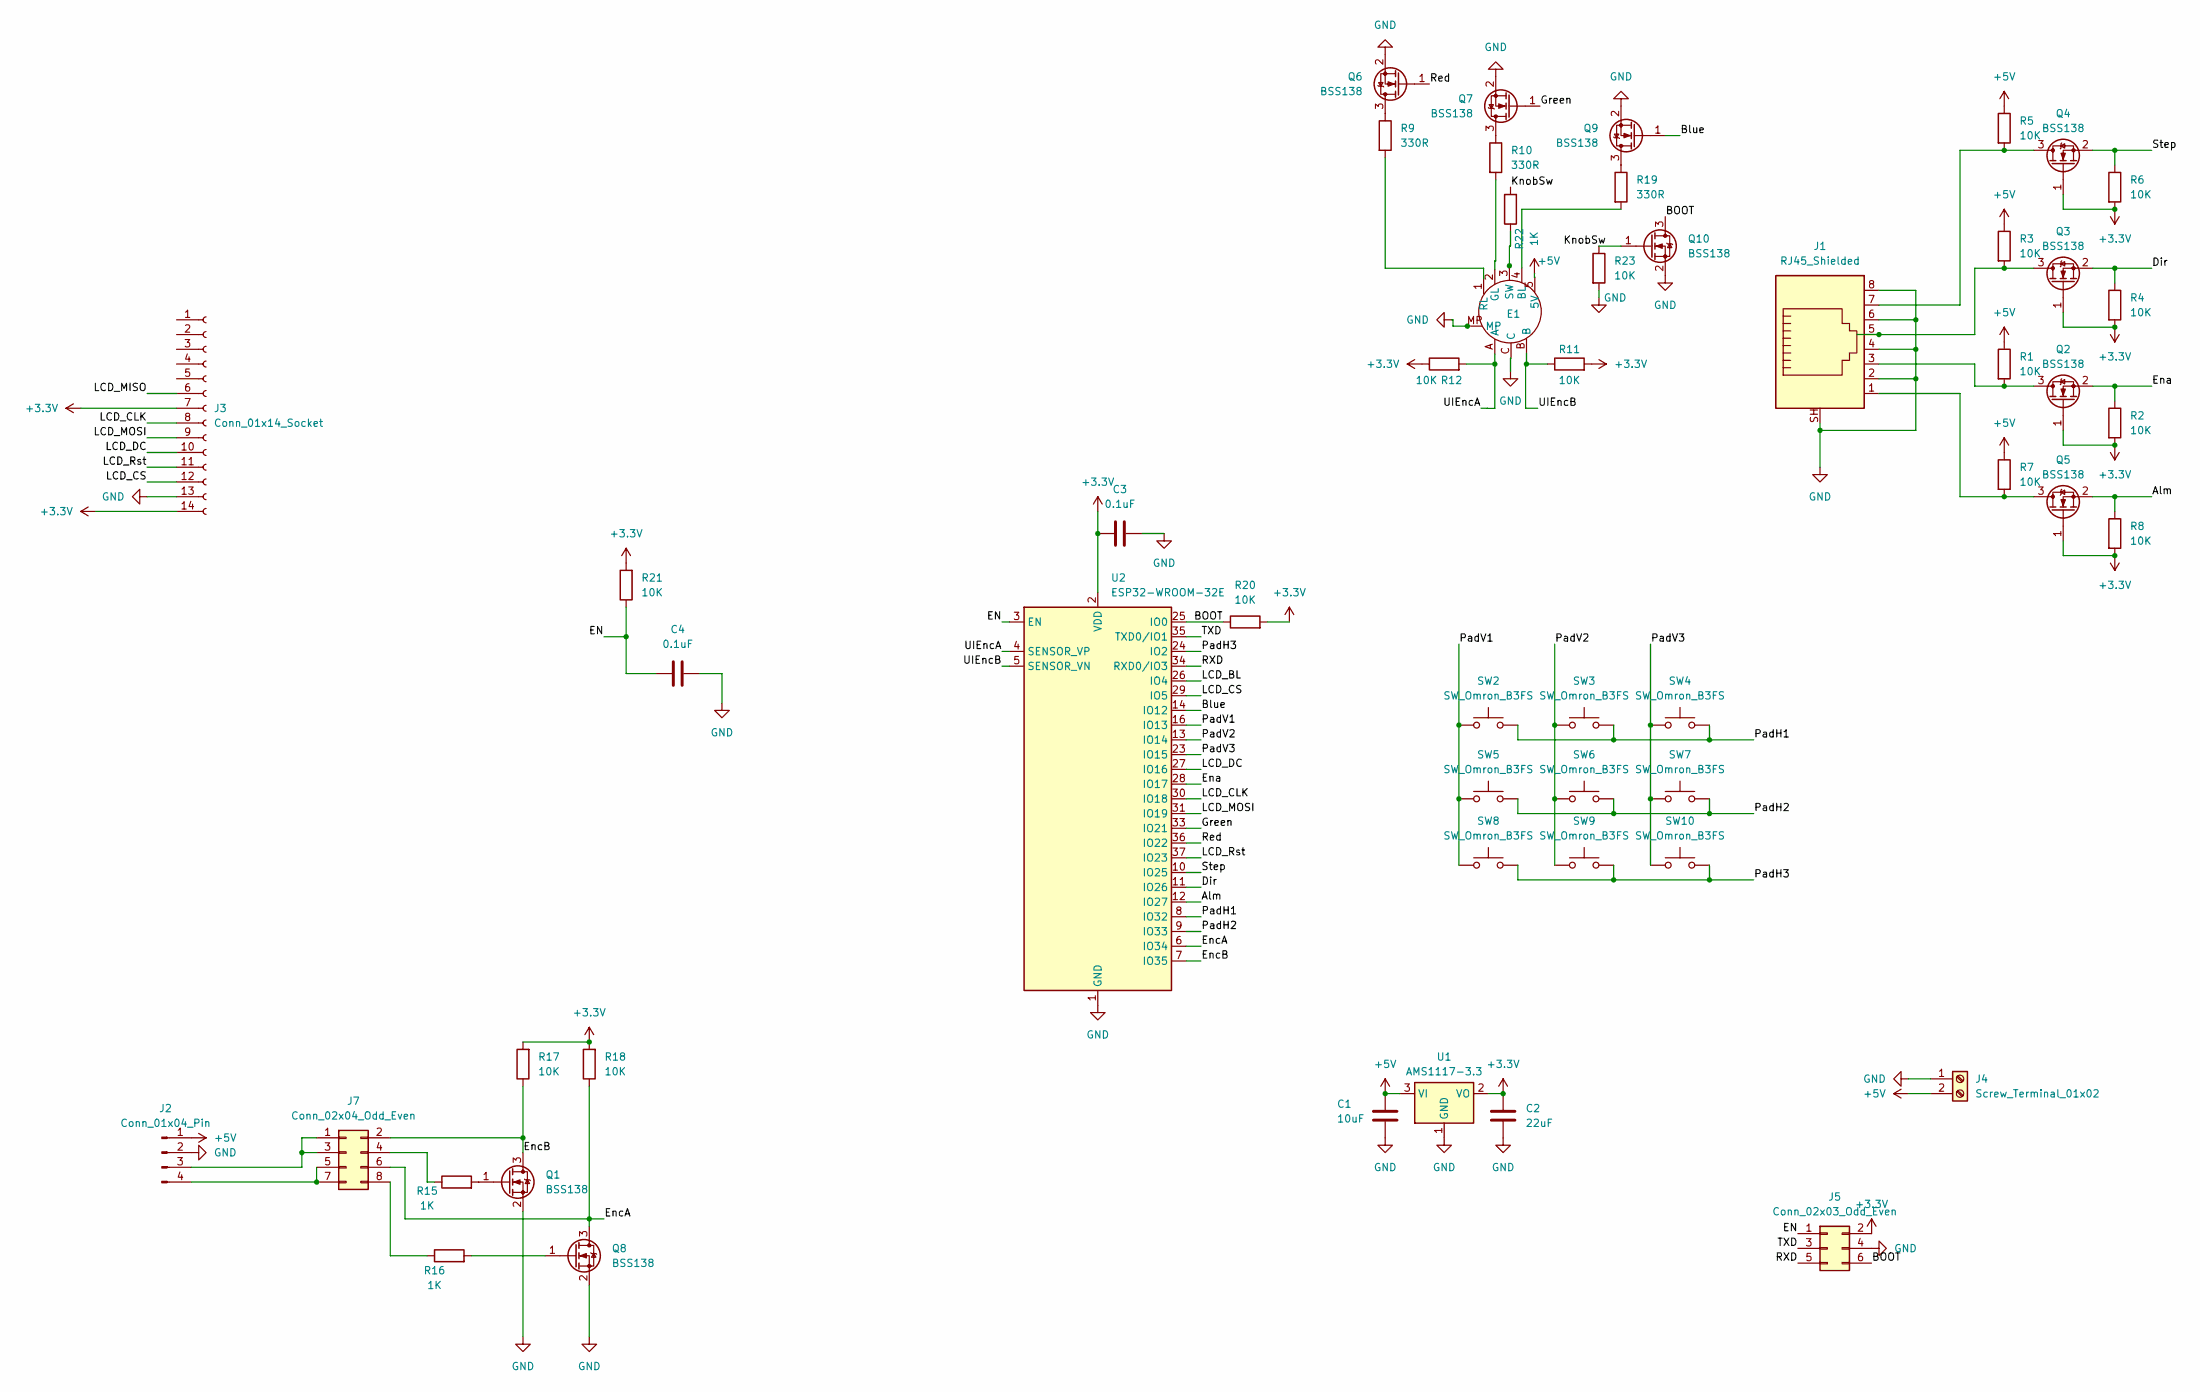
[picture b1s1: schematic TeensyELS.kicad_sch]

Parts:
C1: 10uF; C_0805_2012Metric
C2: 22uF; C_0805_2012Metric
C3, C4: 0.1uF; C_0805_2012Metric
E1: Sparkfun
J1: RJ45_Shielded; RJ45_RCH_RC01937
J2: Conn_01x04_Pin; JST_XH_B4B-XH-A_1x04_P2.50mm_Vertical
J3: Conn_01x14_Socket; PinHeader_1x14_P2.54mm_Vertical
J4: Screw_Terminal_01x02; TerminalBlock_CUI_TB007-508-02_1x02_P5.08mm_Horizontal
J5: Conn_02x03_Odd_Even; PinHeader_2x03_P1.27mm_Horizontal
J7: Conn_02x04_Odd_Even; PinHeader_2x04_P2.54mm_Vertical
Q1, Q2, Q3, Q4, Q5, Q6, Q7, Q8, Q9, Q10: BSS138; SOT-23
R1, R2, R3, R4, R5, R6, R7, R8, R11, R12, R17, R18, R20, R21, R23: 10K; R_0805_2012Metric
R9, R10, R19: 330R; R_0805_2012Metric
R15, R16, R22: 1K; R_0805_2012Metric
SW2, SW3, SW4, SW5, SW6, SW7, SW8, SW9, SW10: SW_Omron_B3FS; SW_TH_Tactile_Omron_B3F-10xx
U1: AMS1117-3.3; SOT-223-3_TabPin2
U2: ESP32-WROOM-32E; ESP32-WROOM-32D

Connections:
+3.3V: C2.2, C3.1, J3.7, J3.14, J5.2, Q2.1 (G), Q3.1 (G), Q4.1 (G), Q5.1 (G), R2.2, R4.2, R6.2, R8.2, R11.2, R12.1, R17.2, R18.2, R20.2, R21.2, U1.2 (VO), U2.2 (VDD)
+5V: C1.2, E1.5 (5V), J2.1, J4.2, R1.1, R3.1, R5.1, R7.1, U1.3 (VI)
/Alm: Q5.2 (S), R8.1, U2.12 (IO27)
/BOOT: J5.6, Q10.3 (D), R20.1, U2.25 (IO0)
/Blue: Q9.1 (G), U2.14 (IO12)
/Dir: Q3.2 (S), R4.1, U2.11 (IO26)
/EN: C4.1, J5.1, R21.1, U2.3 (EN)
/Ena: Q2.2 (S), R2.1, U2.28 (IO17)
/EncA: J7.6, Q8.3 (D), R18.1, U2.6 (IO34)
/EncB: J7.2, Q1.3 (D), R17.1, U2.7 (IO35)
/Green: Q7.1 (G), U2.33 (IO21)
/KnobSw: Q10.1 (G), R22.2, R23.1
/LCD_BL: U2.26 (IO4)
/LCD_CLK: J3.8, U2.30 (IO18)
/LCD_CS: J3.12, U2.29 (IO5)
/LCD_DC: J3.10, U2.27 (IO16)
/LCD_MISO: J3.6
/LCD_MOSI: J3.9, U2.31 (IO19)
/LCD_Rst: J3.11, U2.37 (IO23)
/PadH1: SW2.2, SW3.2, SW4.2, U2.8 (IO32)
/PadH2: SW5.2, SW6.2, SW7.2, U2.9 (IO33)
/PadH3: SW8.2, SW9.2, SW10.2, U2.24 (IO2)
/PadV1: SW2.1, SW5.1, SW8.1, U2.16 (IO13)
/PadV2: SW3.1, SW6.1, SW9.1, U2.13 (IO14)
/PadV3: SW4.1, SW7.1, SW10.1, U2.23 (IO15)
/RXD: J5.5, U2.34 (RXD0/IO3)
/Red: Q6.1 (G), U2.36 (IO22)
/Step: Q4.2 (S), R6.1, U2.10 (IO25)
/TXD: J5.3, U2.35 (TXD0/IO1)
/UIEncA: E1.A, R12.2, U2.4 (SENSOR_VP)
/UIEncB: E1.B, R11.1, U2.5 (SENSOR_VN)
GND: C1.1, C2.1, C3.2, C4.2, E1.C, E1.MP, J1.2, J1.4, J1.6, J1.8, J1.SH, J2.2, J3.13, J4.1, J5.4, Q1.2 (S), Q6.2 (S), Q7.2 (S), Q8.2 (S), Q9.2 (S), Q10.2 (S), R23.2, U1.1 (GND), U2.1 (GND), U2.15 (GND), U2.38 (GND), U2.39 (GND)
unnamed: E1.4 (BL), R19.2
unnamed: E1.2 (GL), R10.2
unnamed: E1.1 (RL), R9.2
unnamed: E1.3 (SW), R22.1
unnamed: J2.3, J7.1, J7.3
unnamed: J2.4, J7.5, J7.7
unnamed: J7.4, R15.1
unnamed: J7.8, R16.1
unnamed: Q1.1 (G), R15.2
unnamed: J1.3, Q2.3 (D), R1.2
unnamed: J1.5, Q3.3 (D), R3.2
unnamed: J1.7, Q4.3 (D), R5.2
unnamed: J1.1, Q5.3 (D), R7.2
unnamed: Q6.3 (D), R9.1
unnamed: Q7.3 (D), R10.1
unnamed: Q8.1 (G), R16.2
unnamed: Q9.3 (D), R19.1

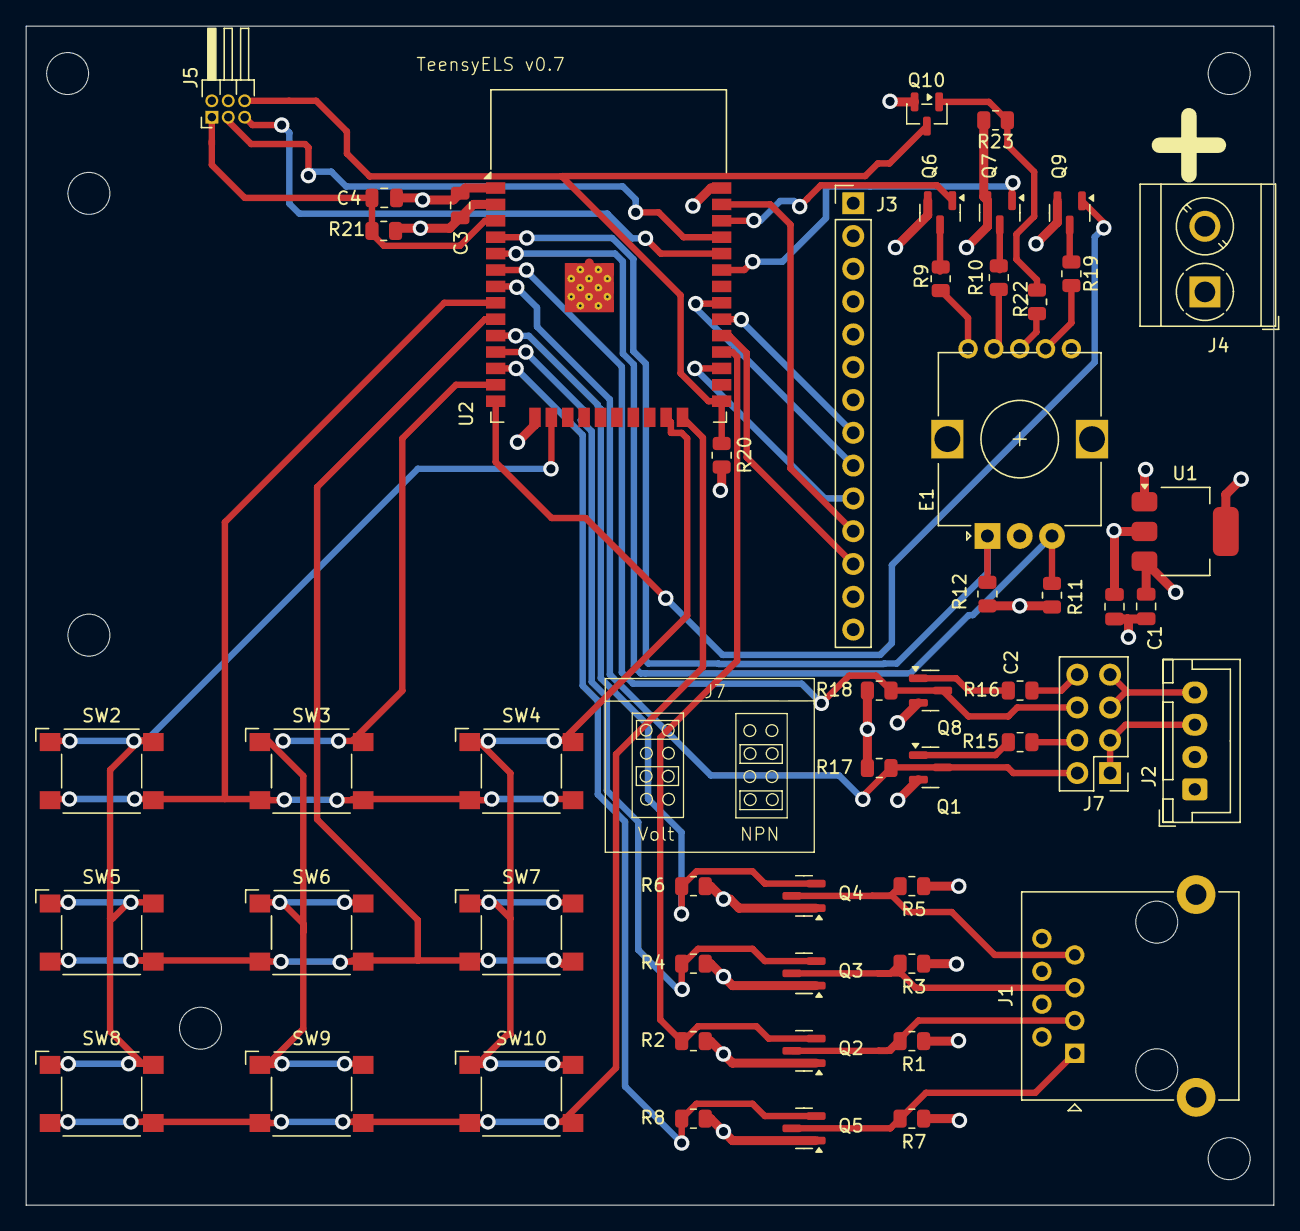
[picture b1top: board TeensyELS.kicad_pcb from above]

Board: 4 copper layers, 96.6 x 91.3 mm, 53 parts (0 on the bottom side), 47 nets.

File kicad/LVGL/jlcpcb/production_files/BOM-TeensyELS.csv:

Comment,Designator,Footprint,LCSC,Quantity
0.1uF,"C3,C4",C_0805_2012Metric,C49678,2
0K,"R13,R14",R_0805_2012Metric,C17477,2
10K,"R1,R11,R12,R17,R18,R2,R20,R21,R3,R4,R5,R6,R7,R8",R_0805_2012Metric,C17414,14
10uF,C1,C_0805_2012Metric,C15850,1
22uF,C2,C_0805_2012Metric,C45783,1
330R,"R10,R19,R9",R_0805_2012Metric,C17630,3
AMS1117-3.3,U1,SOT-223-3_TabPin2,C6186,1
BSS138,"Q2,Q3,Q4,Q5,Q6,Q7,Q9",SOT-23,C7420339,7
Conn_02x03_Odd_Even,J5,PinHeader_2x03_P1.27mm_Vertical_SMD,C42372553,1
ESP32-WROOM-32E,U2,ESP32-WROOM-32D,C701342,1
SW_Omron_B3FS,"SW1,SW10,SW2,SW3,SW4,SW5,SW6,SW7,SW8,SW9",SW_SPST_Omron_B3FS-101xP,C231324,10
